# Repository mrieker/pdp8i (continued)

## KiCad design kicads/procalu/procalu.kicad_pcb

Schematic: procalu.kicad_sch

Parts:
C1, C2, C3, C4, C5, C6, C7, C8, C9, C10, C11, C12, C13, C14, C15, C16, C17, C18, C19, C20, C21, C22, C23, C24, C25, C26, C27, C28, C29, C30, C31, C32, C33, C34, C35, C36, C37, C38, C39, C40, C41, C42, C43, C44, C45, C46, C47, C48, C49, C50, C51, C52, C53, C54, C55, C56, C57, C58, C59, C60, C61, C62, C63, C64, C65, C66, C67, C68, C69, C70, C71, C72, C73, C74, C75, C76: C; R_Axial_DIN0207_L6.3mm_D2.5mm_P7.62mm_Horizontal
E11, E21, E31, E41, E51, E61, E71, E81, E91, E101, E111: 74AHC540; DIP-20_W7.62mm
E12, E42, E72: 74AHC86; DIP-14_W7.62mm
E13, E85: 74AHC138; DIP-16_W7.62mm
E14: 74AHC02
E15, E74, E87, E94, E103, E104: 74AHC04; DIP-14_W7.62mm
E16, E17, E18, E27, E68, E75, E95: 74AC10; DIP-14_W7.62mm
E22, E52, E73: 74AHC157; DIP-16_W7.62mm
E23, E24, E32, E36, E43, E44, E45, E56, E62, E63, E64, E82: 74AC153; DIP-16_W7.62mm
E25, E33, E46, E55, E66: 74AHC08; DIP-14_W7.62mm
E26: 74AC11; DIP-14_W7.62mm
E28, E78: 74AC20; DIP-14_W7.62mm
E34, E54, E65: 74AC283; DIP-16_W7.62mm
E35, E53, E67, E83: 74AHC32; DIP-14_W7.62mm
E37, E77: 74HC27; DIP-14_W7.62mm
E38, E57, E86, E88, E92, E96: 74AHC00; DIP-14_W7.62mm
E47: 74HC21; DIP-14_W7.62mm
E48, E84: 74AHC02; DIP-14_W7.62mm
E58, E76, E105: 74HC30; DIP-14_W7.62mm
E93: 74HC4075; DIP-14_W7.62mm
E102: 74HC42; DIP-16_W7.62mm
J1, J2, J3, J4: Conn_01x36; PinHeader_1x36_P2.54mm_Vertical

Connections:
/AA: E37.9, E38.6, E84.12
/BB: E74.9, E84.9, E105.8
/CC: E84.8, E95.8
/CC3: E92.12, E93.4, E94.10
/CONSCK: J4.35
/CONSDA: J4.34
/EE: E48.8, E68.8
/FF: E28.6, E48.2, E48.5, E48.9
/HH: E77.2, E77.10, E83.11
/JJ: E48.3, E48.6, E58.8, E77.11, E77.13
/KK: E26.8, E37.11
/LL: E77.9, E78.8
/MM: E18.8, E77.1
/NN: E15.8, E37.10, E57.1
/_AA1: E17.8, E38.4
/_AA2: E38.5, E88.6
/_ACCLEAR: E91.2 (A0), J3.28
/_ACUM_0: E81.4 (A2), J3.7
/_ACUM_1: E71.7 (A5), J2.34
/_ACUM_2: E71.2 (A0), J2.27
/_ACUM_3: E61.5 (A3), J2.20
/_ACUM_4: E51.8 (A6), J2.13
/_ACUM_5: E51.3 (A1), J2.7
/_ACUM_6: E41.6 (A4), J1.35
/_ACUM_7: E31.9 (A7), J1.29
/_ACUM_8: E31.4 (A2), J1.23
/_ACUM_9: E21.6 (A4), J1.16
/_ACUM_10: E11.8 (A6), J1.9
/_ACUM_11: E11.2 (A0), J1.2
/_BB1: E94.8, E105.2
/_BB2: E104.8, E105.6
/_BB3: E95.6, E105.12
/_BB4: E96.3, E105.11
/_BB5: E83.8, E105.1
/_BB6: E93.10, E105.3
/_BRKCYC: J4.33
/_BRKRQST: J3.29
/_BRKWRM: E101.2 (A0), J4.11
/_BUSINI: J3.31
/_BWCOV: J3.32
/_CAINC: E101.3 (A1), J4.12
/_CC1: E95.9, E96.6, E96.9
/_CC2: E95.10, E96.10, E96.11
/_CC3: E67.9, E75.8, E94.11, E95.11
/_CLOCK: J4.6
/_CYCLE3: E101.4 (A2), J4.13
/_DFLD_0: J3.22
/_DFLD_1: J3.18
/_DFLD_2: J3.14
/_DMAFLD_0: J3.23
/_EE1: E27.12, E68.10
/_EE2: E68.11, E68.12
/_EE3: E68.9, E88.8
/_FF1: E27.8, E28.2
/_FF2: E16.8, E28.1
/_FF3: E28.4, E38.3
/_FF4: E28.5, E95.12
/_IFLD_0: J3.24
/_IFLD_1: J3.20
/_IFLD_2: J3.16
/_INBUS_0: E81.7 (A5), J3.10
/_INBUS_1: E81.2 (A0), J3.3
/_INBUS_2: E71.5 (A3), J2.30
/_INBUS_3: E61.8 (A6), J2.23
/_INBUS_4: E61.3 (A1), J2.16
/_INBUS_5: E51.6 (A4), J2.10
/_INBUS_6: E41.9 (A7), J2.4
/_INBUS_7: E41.4 (A2), J1.32
/_INBUS_8: E31.7 (A5), J1.26
/_INBUS_9: E21.9 (A7), J1.19
/_INBUS_10: E21.3 (A1), J1.12
/_INBUS_11: E11.5 (A3), J1.5
/_INTINH: J4.15
/_INTRQST: J4.16
/_ION: J3.30
/_IOP: E91.8 (A6), J4.8
/_IOSKIP: J4.17
/_IREG_9: E31.3 (A1), J1.22
/_IREG_10: E21.5 (A3), J1.15
/_IREG_11: E11.7 (A5), J1.8
/_JJ1: E58.5, E92.3
/_JJ2: E57.8, E58.4
/_JJ3: E17.12, E58.1
/_JJ4: E58.6, E86.6
/_JJ5: E57.11, E58.3
/_JJ6: E38.8, E58.2
/_LINK: E91.9 (A7), J4.9
/_LL1: E17.6, E78.13
/_LL2: E78.10, E86.8
/_LL3: E78.9, E88.11
/_LL4: E68.6, E78.12
/_LNKTOG: J4.18
/_MADR_0: E81.5 (A3), J3.8
/_MADR_1: E71.8 (A6), J2.35
/_MADR_2: E71.3 (A1), J2.28
/_MADR_3: E61.6 (A4), J2.21
/_MADR_4: E51.9 (A7), J2.14
/_MADR_5: E51.4 (A2), J2.8
/_MADR_6: E41.7 (A5), J2.2
/_MADR_7: E41.2 (A0), J1.30
/_MADR_8: E31.5 (A3), J1.24
/_MADR_9: E21.7 (A5), J1.17
/_MADR_10: E11.9 (A7), J1.10
/_MADR_11: E11.3 (A1), J1.3
/_MAJST_0: E101.8 (A6), J4.22
/_MAJST_1: E101.7 (A5), J4.21
/_MAJST_2: E101.6 (A4), J4.20
/_MAJST_3: E101.5 (A3), J4.19
/_MBUF_0: E81.6 (A4), J3.9
/_MBUF_1: E71.9 (A7), J3.2
/_MBUF_2: E71.4 (A2), J2.29
/_MBUF_3: E61.7 (A5), J2.22
/_MBUF_4: E61.2 (A0), J2.15
/_MBUF_5: E51.5 (A3), J2.9
/_MBUF_6: E41.8 (A6), J2.3
/_MBUF_7: E41.3 (A1), J1.31
/_MBUF_8: E31.6 (A4), J1.25
/_MBUF_9: E21.8 (A6), J1.18
/_MBUF_10: E21.2 (A0), J1.11
/_MBUF_11: E11.4 (A2), J1.4
/_MEAD_0: J3.25
/_MEAD_1: J3.21
/_MEAD_2: J3.17
/_MEMDIS: J3.26
/_MM1: E18.6, E18.11
/_MM2: E18.9, E88.3
/_MM3: E18.10, E28.8
/_NN1: E15.9, E16.6, E27.3
/_PAUSE: J4.14
/_PCTR_0: E81.8 (A6), J3.12
/_PCTR_1: E81.3 (A1), J3.5
/_PCTR_2: E71.6 (A4), J2.32
/_PCTR_3: E61.9 (A7), J2.25
/_PCTR_4: E61.4 (A2), J2.18
/_PCTR_5: E51.7 (A5), J2.12
/_PCTR_6: E51.2 (A0), J2.6
/_PCTR_7: E41.5 (A3), J1.34
/_PCTR_8: E31.8 (A6), J1.28
/_PCTR_9: E31.2 (A0), J1.21
/_PCTR_10: E21.4 (A2), J1.14
/_PCTR_11: E11.6 (A4), J1.7
/_PP1: E74.13, E75.6
/_PP2: E16.12, E27.4
/_READSR: E81.11 (Y7), J3.27
/_RESET: J4.7
/_RUN: J4.10
/_SWCONT: E91.6 (A4), J4.2
/_SWDEPOS: E91.5 (A3), J3.35
/_SWEXAM: E91.4 (A2), J3.34
/_SWLDAD: E91.3 (A1), J3.33
/_SWSINST: J4.5
/_SWSSTEP: J4.4
/_SWSTART: E91.7 (A5), J4.3
/_TP1: J4.27
/_TP2: J4.28
/_TP3: J4.29
/_TP4: J4.30
/_TS1: E111.2 (A0), J4.23
/_TS2: E111.3 (A1), J4.24
/_TS3: E111.4 (A2), J4.25
/_TS4: E111.5 (A3), J4.26
/_asel_0: E23.14 (S0), E24.14 (S0), E32.14 (S0), E62.14 (S0), E63.14 (S0), E77.8, E78.5, E82.14 (S0)
/_asel_1: E23.2 (S1), E24.2 (S1), E32.2 (S1), E62.2 (S1), E63.2 (S1), E77.12, E78.4, E82.2 (S1)
/_bsel_0: E22.1 (S), E52.1 (S), E73.1 (S), E84.10
/_irand: E13.15 (~Y0), E74.1
/_irdca: E13.12 (~Y3), E15.5
/_iriot: E13.9 (~Y6)
/_irisz: E13.13 (~Y2), E15.13
/_irjmp: E13.10 (~Y5), E14.11, E15.11
/_irjms: E13.11 (~Y4), E15.3
/_iropr: E13.7 (~Y7), E14.8, E28.12, E77.4, E87.3
/_irtad: E13.14 (~Y1), E15.1
/_msdefer: E94.3, E102.3 (2)
/_msdepos: E102.10 (8), E103.9
/_msexec: E94.13, E102.4 (3)
/_msintak: E102.9 (7), E103.5
/_mswrdct: E74.11, E102.5 (4)
/_nxtmsbreak: E85.9 (~Y6), E93.12
/_nxtmswrdct: E83.10, E85.11 (~Y4)
/_ts4: E83.9, E93.13, E94.6
/acclear: E91.18 (Y0), E92.4
/acum_0: E72.9, E81.16 (Y2)
/acum_1: E71.13 (Y5), E72.5
/acum_2: E71.18 (Y0), E72.12
/acum_3: E61.15 (Y3), E72.1
/acum_4: E42.9, E51.12 (Y6)
/acum_5: E42.5, E51.17 (Y1)
/acum_6: E41.14 (Y4), E42.12
/acum_7: E31.11 (Y7), E42.1
/acum_8: E12.9, E31.16 (Y2)
/acum_9: E12.5, E21.14 (Y4)
/acum_10: E11.12 (Y6), E12.13
/acum_11: E11.18 (Y0), E12.1
/acxx_0: E72.8, E82.3 (I3a)
/acxx_1: E72.6, E82.13 (I3b)
/acxx_2: E63.3 (I3a), E72.11
/acxx_3: E63.13 (I3b), E72.3
/acxx_4: E42.8, E62.3 (I3a)
/acxx_5: E42.6, E62.13 (I3b)
/acxx_6: E32.3 (I3a), E42.11
/acxx_7: E32.13 (I3b), E42.3
/acxx_8: E12.8, E23.3 (I3a)
/acxx_9: E12.6, E23.13 (I3b)
/acxx_10: E12.11, E24.3 (I3a)
/acxx_11: E12.3, E24.13 (I3b)
/alua_0: E65.5 (A1), E66.4, E82.7 (Za), E83.2
/alua_1: E55.9, E65.3 (A2), E82.9 (Zb), E83.5
/alua_2: E63.7 (Za), E65.14 (A3), E66.2, E67.2
/alua_3: E63.9 (Zb), E65.12 (A4), E66.13, E67.4
/alua_4: E53.4, E54.5 (A1), E55.4, E62.7 (Za)
/alua_5: E53.9, E54.3 (A2), E55.2, E62.9 (Zb)
/alua_6: E32.7 (Za), E33.9, E53.12, E54.14 (A3)
/alua_7: E32.9 (Zb), E53.1, E54.12 (A4), E55.13
/alua_8: E23.7 (Za), E25.10, E34.5 (A1), E35.12
/alua_9: E23.9 (Zb), E25.13, E34.3 (A2), E35.1
/alua_10: E24.7 (Za), E34.14 (A3), E35.5, E46.5
/alua_11: E24.9 (Zb), E34.12 (A4), E35.10, E46.1
/alub_0: E65.6 (B1), E66.5, E73.4 (Za), E83.1
/alub_1: E55.10, E65.2 (B2), E73.7 (Zb), E83.4
/alub_2: E65.15 (B3), E66.1, E67.1, E73.9 (Zc)
/alub_3: E65.11 (B4), E66.12, E67.5, E73.12 (Zd)
/alub_4: E52.4 (Za), E53.5, E54.6 (B1), E55.5
/alub_5: E52.7 (Zb), E53.10, E54.2 (B2), E55.1
/alub_6: E33.10, E52.9 (Zc), E53.13, E54.15 (B3)
/alub_7: E52.12 (Zd), E53.2, E54.11 (B4), E55.12
/alub_8: E22.4 (Za), E25.9, E34.6 (B1), E35.13
/alub_9: E22.7 (Zb), E25.12, E34.2 (B2), E35.2
/alub_10: E22.9 (Zc), E34.15 (B3), E35.4, E46.4
/alub_11: E22.12 (Zd), E34.11 (B4), E35.9, E46.2
/aluq_0: E64.7 (Za), J3.11
/aluq_1: E64.9 (Zb), J3.4
/aluq_2: E56.7 (Za), J2.31
/aluq_3: E56.9 (Zb), J2.24
/aluq_4: E43.7 (Za), J2.17
/aluq_5: E43.9 (Zb), J2.11
/aluq_6: E44.7 (Za), J2.5
/aluq_7: E44.9 (Zb), J1.33
/aluq_8: E36.7 (Za), J1.27
/aluq_9: E36.9 (Zb), J1.20
/aluq_10: E45.7 (Za), J1.13
/aluq_11: E45.9 (Zb), J1.6
/aluq_12: J3.15
/autoinc: E27.10, E47.6
/azero: E23.1 (Ea), E23.15 (Eb), E24.1 (Ea), E24.15 (Eb), E32.1 (Ea), E32.15 (Eb), E62.1 (Ea), E62.15 (Eb), E63.1 (Ea), E63.15 (Eb), E75.12, E82.1 (Ea), E82.15 (Eb)
/brkwrm: E95.4, E101.18 (Y0)
/bzero: E22.15 (E), E52.15 (E), E73.15 (E), E78.6
/cainc: E95.1, E101.17 (Y1)
/cclears: E84.11, E92.8
/cin: E57.6, E65.7 (C0)
/comac: E12.2, E12.4, E12.10, E12.12, E26.12, E42.2, E42.4, E42.10, E42.13, E72.2, E72.4, E72.10, E72.13
/cout: E34.9 (C4), J3.19
/cycle3: E93.11, E101.16 (Y2)
/dirjmp: E14.13, E18.3
/efaddr_7: E32.11 (I1b), E33.6
/efaddr_8: E23.5 (I1a), E33.3
/efaddr_9: E23.11 (I1b), E33.11
/efaddr_10: E24.5 (I1a), E25.3
/efaddr_11: E24.11 (I1b), E25.6
/extarex: E86.11, E96.13
/group1: E14.10, E16.5, E26.2
/group2: E75.10, E77.6
/inbus_0: E73.2 (I0a), E81.13 (Y5)
/inbus_1: E73.5 (I0b), E81.18 (Y0)
/inbus_2: E71.15 (Y3), E73.11 (I0c)
/inbus_3: E61.12 (Y6), E73.14 (I0d)
/inbus_4: E52.2 (I0a), E61.17 (Y1)
/inbus_5: E51.14 (Y4), E52.5 (I0b)
/inbus_6: E41.11 (Y7), E52.11 (I0c)
/inbus_7: E41.16 (Y2), E52.14 (I0d)
/inbus_8: E22.2 (I0a), E31.13 (Y5)
/inbus_9: E21.11 (Y7), E22.5 (I0b)
/inbus_10: E21.17 (Y1), E22.11 (I0c)
/inbus_11: E11.15 (Y3), E22.14 (I0d)
/iop: E91.12 (Y6), E96.5
/irand: E74.2, E75.3
/irdca: E15.6, E17.11, E26.11
/ireg_9: E13.1 (A0), E31.17 (Y1)
/ireg_10: E13.2 (A1), E21.15 (Y3)
/ireg_11: E11.13 (Y5), E13.3 (A2)
/irisz: E15.12, E16.11
/irjmp: E15.10, E27.1
/irjms: E15.4, E17.2, E17.3
/iropr: E68.4, E76.11, E86.2, E87.4
/irtad: E15.2, E16.13
/link: E91.11 (Y7)
/madr_0: E81.15 (Y3), E82.6 (I0a)
/madr_1: E71.12 (Y6), E82.10 (I0b)
/madr_2: E63.6 (I0a), E71.17 (Y1)
/madr_3: E47.4, E61.14 (Y4), E63.10 (I0b)
/madr_4: E51.11 (Y7), E62.6 (I0a), E84.3
/madr_5: E51.16 (Y2), E62.10 (I0b), E84.2
/madr_6: E32.6 (I0a), E37.4, E41.13 (Y5)
/madr_7: E32.10 (I0b), E33.5, E37.5, E41.18 (Y0)
/madr_8: E23.6 (I0a), E31.15 (Y3), E33.1, E37.3
/madr_9: E21.13 (Y5), E23.10 (I0b), E33.12, E37.2
/madr_10: E11.11 (Y7), E24.6 (I0a), E25.1, E37.1
/madr_11: E11.17 (Y1), E24.10 (I0b), E25.5, E37.13
/majst_0: E101.12 (Y6), E102.15 (A0)
/majst_1: E101.13 (Y5), E102.14 (A1)
/majst_2: E101.14 (Y4), E102.13 (A2)
/majst_3: E84.5, E101.15 (Y3), E102.12 (A3)
/mbuf_0: E57.2, E73.3 (I1a), E76.3, E77.3, E81.14 (Y4), E82.5 (I1a)
/mbuf_1: E71.11 (Y7), E73.6 (I1b), E74.3, E82.11 (I1b)
/mbuf_2: E63.5 (I1a), E67.10, E71.16 (Y2), E73.10 (I1c), E74.5
/mbuf_3: E61.13 (Y5), E63.11 (I1b), E73.13 (I1d)
/mbuf_4: E52.3 (I1a), E61.18 (Y0), E62.5 (I1a)
/mbuf_5: E26.1, E51.15 (Y3), E52.6 (I1b), E62.11 (I1b)
/mbuf_6: E32.5 (I1a), E41.12 (Y6), E52.10 (I1c)
/mbuf_7: E25.2, E25.4, E33.2, E33.4, E33.13, E41.17 (Y1), E52.13 (I1d), E92.13
/mbuf_8: E14.9, E14.12, E22.3 (I1a), E31.14 (Y4), E76.12, E87.1
/mbuf_9: E21.12 (Y6), E22.6 (I1b)
/mbuf_10: E21.18 (Y0), E22.10 (I1c)
/mbuf_11: E11.16 (Y2), E22.13 (I1d)
/memacsw: J2.19
/msbreak: E95.5, E103.10
/mscurad: E88.9, E95.13, E103.12
/msdefer: E27.9, E27.13, E68.1, E94.4
/msdepos: E57.9, E66.9, E96.2, E103.8
/msexam: E92.2, E103.4
/msexec: E16.2, E16.10, E17.4, E17.10, E17.13, E26.9, E75.5, E86.1, E94.12
/msfetch: E16.3, E18.5, E26.13, E28.13, E75.9, E76.1, E103.2
/msintak: E86.4, E86.9, E103.6
/mswrdct: E38.1, E38.10, E57.13, E74.10
/nxtms_0: E85.1 (A0), J3.13
/nxtms_1: E85.2 (A1), J3.6
/nxtms_2: E85.3 (A2), J2.33
/nxtms_3: E85.4 (~E0), J2.26
/nxtmsdefer: E87.6, E88.2
/nxtmsexec: E28.9, E68.5, E68.13, E87.12
/nxtmsfetch: E87.10, E88.13
/nxtmsintak: E87.8, E88.5
/pctr_0: E81.12 (Y6), E82.4 (I2a)
/pctr_1: E81.17 (Y1), E82.12 (I2b)
/pctr_2: E63.4 (I2a), E71.14 (Y4)
/pctr_3: E61.11 (Y7), E63.12 (I2b)
/pctr_4: E61.16 (Y2), E62.4 (I2a)
/pctr_5: E51.13 (Y5), E62.12 (I2b)
/pctr_6: E32.4 (I2a), E51.18 (Y0)
/pctr_7: E32.12 (I2b), E41.15 (Y3)
/pctr_8: E23.4 (I2a), E31.12 (Y6)
/pctr_9: E23.12 (I2b), E31.18 (Y0)
/pctr_10: E21.16 (Y2), E24.4 (I2a)
/pctr_11: E11.14 (Y4), E24.12 (I2b)
/qsel_0: E36.14 (S0), E43.14 (S0), E44.14 (S0), E45.14 (S0), E56.14 (S0), E64.14 (S0), E74.12
/qsel_1: E27.6, E36.2 (S1), E43.2 (S1), E44.2 (S1), E45.2 (S1), E56.2 (S1), E64.2 (S1)
/qsum_0: E64.4 (I2a), E65.4 (S1)
/qsum_1: E64.12 (I2b), E65.1 (S2)
/qsum_2: E56.4 (I2a), E65.13 (S3)
/qsum_3: E56.12 (I2b), E65.10 (S4)
/readsr: E81.9 (A7), E93.6
/swcont: E91.14 (Y4), E94.1
/swcontx: E83.13, E84.4
/swdepos: E57.10, E91.15 (Y3)
/swexam: E91.16 (Y2), E92.1
/swldad: E91.17 (Y1), E93.5, E94.9
/swstart: E83.12, E91.13 (Y5)
/ts1: E104.9, E111.18 (Y0)
/ts2: E16.9, E17.5, E26.10, E27.11, E38.2, E66.10, E86.10, E95.2, E95.3, E96.1, E111.17 (Y1)
/ts3: E16.1, E16.4, E17.1, E17.9, E18.4, E27.2, E57.12, E75.4, E75.11, E86.5, E96.4, E96.12, E111.16 (Y2)
/ts4: E28.10, E38.9, E68.2, E68.3, E88.1, E88.4, E88.10, E88.12, E94.5, E111.15 (Y3)
GND: C1.2, C2.2, C3.2, C4.2, C5.2, C6.2, C7.2, C8.2, C9.2, C10.2, C11.2, C12.2, C13.2, C14.2, C15.2, C16.2, C17.2, C18.2, C19.2, C20.2, C21.2, C22.2, C23.2, C24.2, C25.2, C26.2, C27.2, C28.2, C29.2, C30.2, C31.2, C32.2, C33.2, C34.2, C35.2, C36.2, C37.2, C38.2, C39.2, C40.2, C41.2, C42.2, C43.2, C44.2, C45.2, C46.2, C47.2, C48.2, C49.2, C50.2, C51.2, C52.2, C53.2, C54.2, C55.2, C56.2, C57.2, C58.2, C59.2, C60.2, C61.2, C62.2, C63.2, C64.2, C65.2, C66.2, C67.2, C68.2, C69.2, C70.2, C71.2, C72.2, C73.2, C74.2, C75.2, C76.2, E11.1 (G1), E11.10 (GND), E11.19 (G2), E12.7 (GND), E13.4 (~E0), E13.5 (~E1), E13.8 (GND), E14.2, E14.3, E14.5, E14.6, E14.7 (GND), E15.7 (GND), E16.7 (GND), E17.7 (GND), E18.1, E18.2, E18.7 (GND), E18.13, E21.1 (G1), E21.10 (GND), E21.19 (G2), E22.8 (GND), E23.8 (GND), E24.8 (GND), E25.7 (GND), E26.3, E26.4, E26.5, E26.7 (GND), E27.7 (GND), E28.7 (GND), E31.1 (G1), E31.10 (GND), E31.19 (G2), E32.8 (GND), E33.7 (GND), E34.8 (GND), E35.7 (GND), E36.1 (Ea), E36.3 (I3a), E36.8 (GND), E36.13 (I3b), E36.15 (Eb), E37.7 (GND), E38.7 (GND), E38.12, E38.13, E41.1 (G1), E41.10 (GND), E41.19 (G2), E42.7 (GND), E43.1 (Ea), E43.3 (I3a), E43.8 (GND), E43.13 (I3b), E43.15 (Eb), E44.1 (Ea), E44.3 (I3a), E44.8 (GND), E44.13 (I3b), E44.15 (Eb), E45.1 (Ea), E45.3 (I3a), E45.8 (GND), E45.13 (I3b), E45.15 (Eb), E46.7 (GND), E46.9, E46.10, E46.12, E46.13, E47.7 (GND), E47.9, E47.10, E47.12, E47.13, E48.7 (GND), E48.11, E48.12, E51.1 (G1), E51.10 (GND), E51.19 (G2), E52.8 (GND), E53.7 (GND), E54.8 (GND), E55.7 (GND), E56.1 (Ea), E56.3 (I3a), E56.8 (GND), E56.13 (I3b), E56.15 (Eb), E57.7 (GND), E58.7 (GND), E61.1 (G1), E61.10 (GND), E61.19 (G2), E62.8 (GND), E63.8 (GND), E64.1 (Ea), E64.3 (I3a), E64.8 (GND), E64.13 (I3b), E64.15 (Eb), E65.8 (GND), E66.7 (GND), E67.7 (GND), E67.12, E67.13, E68.7 (GND), E71.1 (G1), E71.10 (GND), E71.19 (G2), E72.7 (GND), E73.8 (GND), E74.7 (GND), E75.7 (GND), E76.7 (GND), E77.7 (GND), E78.7 (GND), E81.1 (G1), E81.10 (GND), E81.19 (G2), E82.8 (GND), E83.7 (GND), E84.7 (GND), E85.5 (~E1), E85.8 (GND), E86.7 (GND), E87.7 (GND), E88.7 (GND), E91.1 (G1), E91.10 (GND), E91.19 (G2)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
unnamed: E27.5, E48.1
unnamed: E34.7 (C0), E54.9 (C4)
unnamed: E34.4 (S1), E36.4 (I2a)
unnamed: E34.1 (S2), E36.12 (I2b)
unnamed: E34.13 (S3), E45.4 (I2a)
unnamed: E34.10 (S4), E45.12 (I2b)
unnamed: E35.11, E36.6 (I0a)
unnamed: E35.3, E36.10 (I0b)
unnamed: E25.8, E36.5 (I1a)
unnamed: E25.11, E36.11 (I1b)
unnamed: E37.6, E47.2
unnamed: E37.8, E78.1
unnamed: E37.12, E47.1
unnamed: E43.6 (I0a), E53.6
unnamed: E43.10 (I0b), E53.8
unnamed: E43.5 (I1a), E55.6
unnamed: E43.11 (I1b), E55.3
unnamed: E43.4 (I2a), E54.4 (S1)
unnamed: E43.12 (I2b), E54.1 (S2)
unnamed: E44.6 (I0a), E53.11
unnamed: E44.10 (I0b), E53.3
unnamed: E33.8, E44.5 (I1a)
unnamed: E44.11 (I1b), E55.11
unnamed: E44.4 (I2a), E54.13 (S3)
unnamed: E44.12 (I2b), E54.10 (S4)
unnamed: E35.6, E45.6 (I0a)
unnamed: E35.8, E45.10 (I0b)
unnamed: E45.5 (I1a), E46.6
unnamed: E45.11 (I1b), E46.3
unnamed: E47.5, E84.1
unnamed: E48.4, E57.5
unnamed: E48.10, E75.13
unnamed: E54.7 (C0), E65.9 (C4)
unnamed: E56.6 (I0a), E67.3
unnamed: E56.10 (I0b), E67.6
unnamed: E56.5 (I1a), E66.3
unnamed: E56.11 (I1b), E66.11
unnamed: E57.3, E57.4
unnamed: E64.6 (I0a), E83.3
unnamed: E64.10 (I0b), E83.6
unnamed: E64.5 (I1a), E66.6
unnamed: E55.8, E64.11 (I1b)
unnamed: E66.8, E93.3
unnamed: E67.8, E78.2
unnamed: E74.4, E76.4
unnamed: E74.6, E76.6
unnamed: E74.8, E75.1
unnamed: E75.2, E84.13
unnamed: E76.8, E86.12
unnamed: E77.5, E87.2
unnamed: E84.6, E94.2
unnamed: E85.14 (~Y1), E87.11
unnamed: E85.13 (~Y2), E87.5
unnamed: E85.12 (~Y3), E87.13
unnamed: E85.7 (~Y7), E87.9
unnamed: E86.3, E86.13
unnamed: E92.5, E96.8
unnamed: E92.6, E92.9
unnamed: E92.10, E92.11
unnamed: E102.2 (1), E103.1
unnamed: E102.6 (5), E103.13
unnamed: E102.7 (6), E103.11
unnamed: E102.11 (9), E103.3
VCC: C1.1, C2.1, C3.1, C4.1, C5.1, C6.1, C7.1, C8.1, C9.1, C10.1, C11.1, C12.1, C13.1, C14.1, C15.1, C16.1, C17.1, C18.1, C19.1, C20.1, C21.1, C22.1, C23.1, C24.1, C25.1, C26.1, C27.1, C28.1, C29.1, C30.1, C31.1, C32.1, C33.1, C34.1, C35.1, C36.1, C37.1, C38.1, C39.1, C40.1, C41.1, C42.1, C43.1, C44.1, C45.1, C46.1, C47.1, C48.1, C49.1, C50.1, C51.1, C52.1, C53.1, C54.1, C55.1, C56.1, C57.1, C58.1, C59.1, C60.1, C61.1, C62.1, C63.1, C64.1, C65.1, C66.1, C67.1, C68.1, C69.1, C70.1, C71.1, C72.1, C73.1, C74.1, C75.1, C76.1, E11.20 (VCC), E12.14 (VCC), E13.6 (E2), E13.16 (VCC), E14.14 (VCC), E15.14 (VCC), E16.14 (VCC), E17.14 (VCC), E18.14 (VCC), E21.20 (VCC), E22.16 (VCC), E23.16 (VCC), E24.16 (VCC), E25.14 (VCC), E26.14 (VCC), E27.14 (VCC), E28.14 (VCC), E31.20 (VCC), E32.16 (VCC), E33.14 (VCC), E34.16 (VCC), E35.14 (VCC), E36.16 (VCC), E37.14 (VCC), E38.14 (VCC), E41.20 (VCC), E42.14 (VCC), E43.16 (VCC), E44.16 (VCC), E45.16 (VCC), E46.14 (VCC), E47.14 (VCC), E48.14 (VCC), E51.20 (VCC), E52.16 (VCC), E53.14 (VCC), E54.16 (VCC), E55.14 (VCC), E56.16 (VCC), E57.14 (VCC), E58.11, E58.12, E58.14 (VCC), E61.20 (VCC), E62.16 (VCC), E63.16 (VCC), E64.16 (VCC), E65.16 (VCC), E66.14 (VCC), E67.14 (VCC), E68.14 (VCC), E71.20 (VCC), E72.14 (VCC), E73.16 (VCC), E74.14 (VCC), E75.14 (VCC), E76.2, E76.5, E76.14 (VCC), E77.14 (VCC), E78.14 (VCC), E81.20 (VCC), E82.16 (VCC), E83.14 (VCC), E84.14 (VCC), E85.6 (E2), E85.16 (VCC), E86.14 (VCC), E87.14 (VCC), E88.14 (VCC), E91.20 (VCC), E92.14 (VCC), E93.14 (VCC), E94.14 (VCC), E95.14 (VCC), E96.14 (VCC), E101.20 (VCC), E102.16 (VCC), E103.14 (VCC), E104.14 (VCC), E105.4, E105.5, E105.14 (VCC), E111.20 (VCC), J1.1, J2.1, J3.1, J4.1

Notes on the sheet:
TS3: ACUM <= ACUM + MBUF
TS4: MADR <= MBUF
TS3: PCTR <= MBUF
TS4: MADR <= INBUS (dma addr)
TS2: MBUF <= INBUS (dma data)
TS4: MADR <= 0
sets ALU to compute MADR + 1 _JJ5 sets up the add in TS3 but does not clock into MADR at TP3 _JJ6 continues the add in TS4 then gets clocked into MADR at TP4
(efaddr_2)
// _MQUO_0
TS3: ACUM <= ACUM | INBUS (io data)
gate SWREG onto INBUS * during TS3 of Group2 for OSR * while LDAD held down to load MADR * during TS2 while doing deposit
// _SCTR_1
// _SCTR_2
TS3: ACUM <= 0
// _MQUO_2
TS3: PCTR <= MADR + 1
LSB
(efaddr_0)
TS2: MBUF <= INBUS (swREG)
// _MQUO_5
// _SCTR_4
// _DMAFLD_2
// _DMAFLD_1
// _MQUO_8
asserted (low) when doing Group2 CLA
TS3 msfetch group1 IAC
// _MQUO_10
MSB
TS1: MBUF <= INBUS (mem data)
(efaddr_3)
// _MQUO_4
TS2: MBUF <= PCTR
// _MQUO_11
TS4: MADR <= efaddr
(efaddr_1)
TS4: MADR <= PCTR
low when doing Group2 with OSR bit low blocking SR coming in on INBUS
TS3: ACUM <= ACUM & MBUF
TS3: PCTR <= efaddr
// _MQUO_3

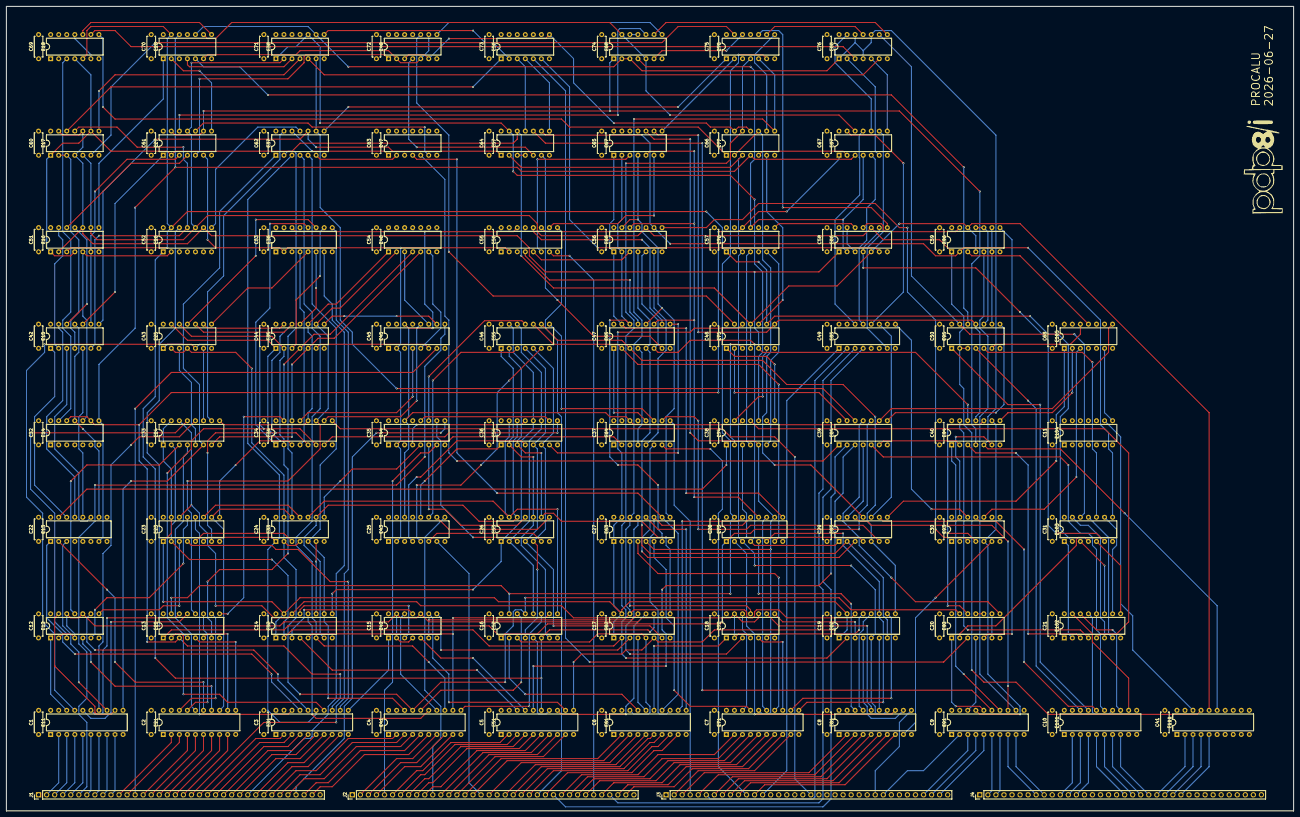
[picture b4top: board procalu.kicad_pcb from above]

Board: 4 copper layers, 406.4 x 254.0 mm, 156 parts (0 on the bottom side), 389 nets.

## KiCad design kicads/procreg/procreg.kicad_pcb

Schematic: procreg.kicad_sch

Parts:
C11, C12, C13, C14, C15, C16, C17, C18, C21, C22, C23, C24, C25, C26, C27, C28, C31, C32, C33, C34, C35, C36, C37, C38, C41, C42, C43, C44, C45, C46, C47, C48, C51, C52, C53, C54, C55, C56, C57, C58, C61, C62, C63, C64, C65, C66, C67, C68, C71, C72, C73, C74, C75, C76, C77, C78, C81, C82, C83, C84, C85, C86, C87, C88, C91, C92, C93, C94, C95, C96, C101: C; R_Axial_DIN0207_L6.3mm_D2.5mm_P7.62mm_Horizontal
E11, E21, E31, E41, E51, E61, E71, E81, E91, E101: 74AHC540; DIP-20_W7.62mm
E12, E13, E24, E34, E45, E52: 74AHC174; DIP-16_W7.62mm
E14, E15, E16, E17, E18, E25, E26, E27, E28, E35, E36, E37, E38: 74AC151; DIP-16_W7.62mm
E22, E42, E53: 74AC161; DIP-16_W7.62mm
E23, E33, E78: 74HC27; DIP-14_W7.62mm
E32: 74HC175; DIP-16_W7.62mm
E43, E67, E96: 74HC30; DIP-14_W7.62mm
E44: 74HC21; DIP-14_W7.62mm
E46: 74AHC138; DIP-16_W7.62mm
E47, E83, E87, E95: 74AHC04; DIP-14_W7.62mm
E48, E74, E76: 74AC10; DIP-14_W7.62mm
E54, E73: 74AHC08; DIP-14_W7.62mm
E55, E57, E58, E63, E75, E77, E84, E85, E92, E93: 74AHC00; DIP-14_W7.62mm
E56: 74AHC02; DIP-14_W7.62mm
E62, E66, E86: 74AC20; DIP-14_W7.62mm
E64: 74AHC86; DIP-14_W7.62mm
E65: 74AC11; DIP-14_W7.62mm
E68: 74AHC04
E72: 74AHC74
E82: 74AHC74; DIP-14_W7.62mm
E88: 74AHC32; DIP-14_W7.62mm
E94: 74HC42; DIP-16_W7.62mm
J1, J2, J3, J4: Conn_01x36; PinHeader_1x36_P2.54mm_Vertical

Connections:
/CONSCK: J4.35
/CONSDA: J4.34
/_ACCLEAR: J3.28
/_ACUM_0: E71.16 (Y2), J3.7
/_ACUM_1: E61.12 (Y6), J2.34
/_ACUM_2: E61.16 (Y2), J2.27
/_ACUM_3: E51.12 (Y6), J2.20
/_ACUM_4: E51.16 (Y2), J2.13
/_ACUM_5: E41.12 (Y6), J2.7
/_ACUM_6: E41.16 (Y2), J1.35
/_ACUM_7: E31.12 (Y6), J1.29
/_ACUM_8: E31.16 (Y2), J1.23
/_ACUM_9: E21.14 (Y4), J1.16
/_ACUM_10: E11.12 (Y6), J1.9
/_ACUM_11: E11.18 (Y0), J1.2
/_BRKCYC: E101.11 (Y7), J4.33
/_BRKRQST: J3.29
/_BRKWRM: E81.9 (A7), J4.11
/_BUSINI: E71.8 (A6), J3.31
/_BWCOV: E71.11 (Y7), J3.32
/_CAINC: E91.2 (A0), J4.12
/_CLOCK: J4.6
/_CYCLE3: J4.13
/_DFLD_0: J3.22
/_DFLD_1: J3.18
/_DFLD_2: J3.14
/_DMAFLD_0: J3.23
/_DMAFLD_2: J3.15
/_IFLD_0: J3.24
/_IFLD_1: J3.20
/_IFLD_2: J3.16
/_INBUS_0: J3.10
/_INBUS_1: J3.3
/_INBUS_2: J2.30
/_INBUS_3: J2.23
/_INBUS_4: J2.16
/_INBUS_5: J2.10
/_INBUS_6: J2.4
/_INBUS_7: J1.32
/_INBUS_8: J1.26
/_INBUS_9: E21.9 (A7), J1.19
/_INBUS_10: E21.3 (A1), J1.12
/_INBUS_11: E11.5 (A3), J1.5
/_INTINH: J4.15
/_INTRQST: J4.16
/_ION: J3.30
/_IOP: E81.6 (A4), J4.8
/_IOSKIP: E91.3 (A1), J4.17
/_IREG_9: E31.17 (Y1), J1.22
/_IREG_10: E21.15 (Y3), J1.15
/_IREG_11: E11.13 (Y5), J1.8
/_LINK: E81.13 (Y5), J4.9
/_LNKTOG: E91.4 (A2), J4.18
/_MADR_0: E71.15 (Y3), J3.8
/_MADR_1: E61.11 (Y7), J2.35
/_MADR_2: E61.15 (Y3), J2.28
/_MADR_3: E51.11 (Y7), J2.21
/_MADR_4: E51.15 (Y3), J2.14
/_MADR_5: E41.11 (Y7), J2.8
/_MADR_6: E41.15 (Y3), J2.2
/_MADR_7: E31.11 (Y7), J1.30
/_MADR_8: E31.15 (Y3), J1.24
/_MADR_9: E21.13 (Y5), J1.17
/_MADR_10: E11.11 (Y7), J1.10
/_MADR_11: E11.17 (Y1), J1.3
/_MAJST_0: E91.8 (A6), J4.22
/_MAJST_1: E91.7 (A5), J4.21
/_MAJST_2: E91.6 (A4), J4.20
/_MAJST_3: E91.5 (A3), J4.19
/_MBUF_0: E71.14 (Y4), J3.9
/_MBUF_1: E71.18 (Y0), J3.2
/_MBUF_2: E61.14 (Y4), J2.29
/_MBUF_3: E61.18 (Y0), J2.22
/_MBUF_4: E51.14 (Y4), J2.15
/_MBUF_5: E51.18 (Y0), J2.9
/_MBUF_6: E41.14 (Y4), J2.3
/_MBUF_7: E41.18 (Y0), J1.31
/_MBUF_8: E31.14 (Y4), J1.25
/_MBUF_9: E21.12 (Y6), J1.18
/_MBUF_10: E21.18 (Y0), J1.11
/_MBUF_11: E11.16 (Y2), J1.4
/_MEAD_0: J3.25
/_MEAD_1: J3.21
/_MEAD_2: J3.17
/_MEMDIS: J3.26
/_PAUSE: J4.14
/_PCTR_0: E71.13 (Y5), J3.12
/_PCTR_1: E71.17 (Y1), J3.5
/_PCTR_2: E61.13 (Y5), J2.32
/_PCTR_3: E61.17 (Y1), J2.25
/_PCTR_4: E51.13 (Y5), J2.18
/_PCTR_5: E51.17 (Y1), J2.12
/_PCTR_6: E41.13 (Y5), J2.6
/_PCTR_7: E41.17 (Y1), J1.34
/_PCTR_8: E31.13 (Y5), J1.28
/_PCTR_9: E31.18 (Y0), J1.21
/_PCTR_10: E21.16 (Y2), J1.14
/_PCTR_11: E11.14 (Y4), J1.7
/_READSR: J3.27
/_RESET: J4.7
/_RUN: E81.8 (A6), J4.10
/_SCTR_0: J3.13
/_SCTR_1: J3.6
/_SCTR_2: J2.33
/_SCTR_3: J2.26
/_SWCONT: E81.5 (A3), J4.2
/_SWDEPOS: E81.4 (A2), J3.35
/_SWEXAM: E81.3 (A1), J3.34
/_SWLDAD: E81.2 (A0), J3.33
/_SWSINST: J4.5
/_SWSSTEP: J4.4
/_SWSTART: J4.3
/_TP1: E101.5 (A3), J4.27
/_TP2: E101.6 (A4), J4.28
/_TP3: E101.7 (A5), J4.29
/_TP4: E101.8 (A6), J4.30
/_TS1: E91.9 (A7), J4.23
/_TS2: E101.2 (A0), J4.24
/_TS3: E101.3 (A1), J4.25
/_TS4: E101.4 (A2), J4.26
/_busini: E54.5, E73.2, E82.13 (~R), E83.4
/_extarex: E76.5, E85.9, E86.2, E95.12
/_irand: E46.15 (~Y0), E48.10
/_irdca: E46.12 (~Y3), E48.11, E48.13
/_iriot: E46.9 (~Y6)
/_irisz: E46.13 (~Y2), E47.13, E48.1
/_irjmp: E46.10 (~Y5), E56.12, E68.11
/_irjms: E46.11 (~Y4), E47.3, E48.2
/_iropr: E46.7 (~Y7), E56.8, E68.5, E78.1
/_irtad: E46.14 (~Y1), E47.11, E48.9
/_ldadclk: E63.3, E63.4, E74.3
/_msdefer: E87.3, E94.3 (2)
/_msdepos: E94.10 (8), E95.11, E96.4
/_msexec: E84.10, E87.1, E94.4 (3)
/_msintak: E47.9, E66.4, E94.9 (7), E96.2
/_mswrdct: E84.9, E94.5 (4), E96.3
/_pcld: E22.9 (~PE), E42.9 (~PE), E53.9 (~PE), E54.3
/_rsel_0: E14.11 (S0), E15.11 (S0), E16.11 (S0), E17.11 (S0), E18.11 (S0), E25.11 (S0), E26.11 (S0), E27.11 (S0), E28.11 (S0), E35.11 (S0), E36.11 (S0), E37.11 (S0), E38.11 (S0), E55.3
/_rsel_1: E14.10 (S1), E15.10 (S1), E16.10 (S1), E17.10 (S1), E18.10 (S1), E25.10 (S1), E26.10 (S1), E27.10 (S1), E28.10 (S1), E35.10 (S1), E36.10 (S1), E37.10 (S1), E38.10 (S1), E55.8
/_rsel_2: E14.9 (S2), E15.9 (S2), E16.9 (S2), E17.9 (S2), E18.9 (S2), E25.9 (S2), E26.9 (S2), E27.9 (S2), E28.9 (S2), E35.9 (S2), E36.9 (S2), E37.9 (S2), E38.9 (S2), E55.11
/_skiplnk: E63.8, E74.2
/_skipneg: E63.11, E74.1
/_skipzer: E43.8, E74.13
/acclk: E24.9 (Cp), E34.9 (Cp), E73.11
/acum_0: E33.11, E34.2 (Q0), E71.4 (A2)
/acum_1: E33.10, E34.5 (Q1), E61.8 (A6)
/acum_2: E33.9, E34.7 (Q2), E61.4 (A2)
/acum_3: E33.5, E34.10 (Q3), E51.8 (A6)
/acum_4: E33.4, E34.12 (Q4), E51.4 (A2)
/acum_5: E33.3, E34.15 (Q5), E41.8 (A6)
/acum_6: E24.2 (Q0), E33.13, E41.4 (A2)
/acum_7: E24.5 (Q1), E31.8 (A6), E33.2
/acum_8: E24.7 (Q2), E31.4 (A2), E33.1
/acum_9: E21.6 (A4), E23.9, E24.10 (Q3)
/acum_10: E11.8 (A6), E23.11, E24.12 (Q4)
/acum_11: E11.2 (A0), E23.10, E24.15 (Q5), E63.13
/aluq_0: E16.13 (I6), E18.15 (I4), E26.14 (I5), E27.2 (I2), E36.12 (I7), E37.1 (I3), E45.3 (D0), E52.3 (D0), E53.3 (D0), J3.11
/aluq_1: E15.13 (I6), E17.15 (I4), E18.14 (I5), E26.12 (I7), E36.1 (I3), E37.2 (I2), E45.4 (D1), E52.4 (D1), E53.4 (D1), J3.4
/aluq_2: E14.13 (I6), E17.14 (I5), E18.12 (I7), E26.1 (I3), E35.15 (I4), E36.2 (I2), E45.6 (D2), E52.6 (D2), E53.5 (D2), J2.31
/aluq_3: E17.12 (I7), E18.1 (I3), E25.15 (I4), E26.2 (I2), E35.14 (I5), E38.13 (I6), E45.11 (D3), E52.11 (D3), E53.6 (D3), J2.24
/aluq_4: E16.15 (I4), E17.1 (I3), E18.2 (I2), E25.14 (I5), E28.13 (I6), E35.12 (I7), E42.3 (D0), E45.13 (D4), E52.13 (D4), J2.17
/aluq_5: E15.15 (I4), E16.14 (I5), E17.2 (I2), E25.12 (I7), E27.13 (I6), E35.1 (I3), E42.4 (D1), E45.14 (D5), E52.14 (D5), J2.11
/aluq_6: E12.3 (D0), E13.3 (D0), E14.15 (I4), E15.14 (I5), E16.12 (I7), E25.1 (I3), E35.2 (I2), E36.13 (I6), E42.5 (D2), J2.5
/aluq_7: E12.4 (D1), E13.4 (D1), E14.14 (I5), E15.12 (I7), E16.1 (I3), E25.2 (I2), E26.13 (I6), E38.15 (I4), E42.6 (D3), J1.33
/aluq_8: E12.6 (D2), E13.6 (D2), E14.12 (I7), E15.1 (I3), E16.2 (I2), E18.13 (I6), E22.3 (D0), E28.15 (I4), E38.14 (I5), J1.27
/aluq_9: E12.11 (D3), E13.11 (D3), E14.1 (I3), E15.2 (I2), E17.13 (I6), E22.4 (D1), E27.15 (I4), E28.14 (I5), E38.12 (I7), J1.20
/aluq_10: E12.13 (D4), E13.13 (D4), E14.2 (I2), E22.5 (D2), E27.14 (I5), E28.12 (I7), E35.13 (I6), E37.15 (I4), E38.1 (I3), J1.13
/aluq_11: E12.14 (D5), E13.14 (D5), E22.6 (D3), E25.13 (I6), E27.12 (I7), E28.1 (I3), E36.15 (I4), E37.14 (I5), E38.2 (I2), J1.6
/aluq_12: E26.15 (I4), E27.1 (I3), E28.2 (I2), E36.14 (I5), E37.12 (I7), E37.13 (I6), E64.3
/autoinc: E44.6, E77.10
/brkcyc: E82.9 (Q), E101.9 (A7)
/brkwrm: E81.11 (Y7), E92.1
/busini: E71.12 (Y6), E83.3
/bwcov: E48.4, E71.9 (A7), E72.5 (Q)
/cainc: E91.18 (Y0), E93.9
/comln: E64.4, E65.6
/cout: E64.1, E72.2 (D), J3.19
/dirjmp: E56.13, E57.4
/extarex: E77.6, E93.13, E95.13
/g2skip: E64.8, E76.1
/group1: E56.10, E62.4, E62.10, E65.4, E65.13, E75.12, E88.2
/group2: E76.13, E78.12, E88.1
/inbus_9: E21.11 (Y7), E32.5 (D1)
/inbus_10: E21.17 (Y1), E32.12 (D2)
/inbus_11: E11.15 (Y3), E47.1
/iop: E75.9, E81.14 (Y4), E87.5
/ioskip: E75.10, E76.9, E91.17 (Y1)
/irandtaddca: E48.8, E58.13
/ireg_9: E31.3 (A1), E32.7 (Q1), E46.1 (A0)
/ireg_10: E21.5 (A3), E32.10 (Q2), E46.2 (A1)
/ireg_11: E11.7 (A5), E32.14 (~Q3), E46.3 (A2)
/irisz: E47.12, E48.3
/irjmp: E68.10, E77.13
/irjms: E47.4, E57.10
/iropr: E67.6, E68.6, E76.11, E77.1
/irtad: E47.10, E58.1
/link: E63.9, E64.5, E81.7 (A5), E82.5 (Q)
/lnclk: E73.8, E82.3 (C)
/lndat: E82.2 (D), E93.3
/lnktog: E91.16 (Y2), E93.12
/madr_0: E52.2 (Q0), E71.5 (A3)
/madr_1: E52.5 (Q1), E61.9 (A7)
/madr_2: E52.7 (Q2), E61.5 (A3)
/madr_3: E44.5, E51.9 (A7), E52.10 (Q3)
/madr_4: E51.5 (A3), E52.12 (Q4), E56.3
/madr_5: E41.9 (A7), E52.15 (Q5), E56.2
/madr_6: E13.2 (Q0), E23.5, E41.5 (A3)
/madr_7: E13.5 (Q1), E23.4, E31.9 (A7)
/madr_8: E13.7 (Q2), E23.3, E31.5 (A3)
/madr_9: E13.10 (Q3), E21.7 (A5), E23.2
/madr_10: E11.9 (A7), E13.12 (Q4), E23.1
/madr_11: E11.3 (A1), E13.15 (Q5), E23.13
/majst_0: E91.12 (Y6), E94.15 (A0)
/majst_1: E91.13 (Y5), E94.14 (A1)
/majst_2: E91.14 (Y4), E94.13 (A2)
/majst_3: E56.5, E83.9, E91.15 (Y3), E94.12 (A3)
/maload: E13.9 (Cp), E52.9 (Cp), E63.6
/mbload: E12.9 (Cp), E45.9 (Cp), E57.11
/mbuf_0: E45.2 (Q0), E67.5, E71.6 (A4), E78.2
/mbuf_1: E45.5 (Q1), E55.1, E68.1, E71.2 (A0)
/mbuf_2: E45.7 (Q2), E55.10, E61.6 (A4), E68.3
/mbuf_3: E45.10 (Q3), E55.13, E61.2 (A0), E64.10
/mbuf_4: E45.12 (Q4), E51.6 (A4), E63.10, E65.3
/mbuf_5: E43.6, E45.15 (Q5), E51.2 (A0)
/mbuf_6: E12.2 (Q0), E41.6 (A4), E62.13, E63.12
/mbuf_7: E12.5 (Q1), E41.2 (A0), E62.1
/mbuf_8: E12.7 (Q2), E31.6 (A4), E56.9, E56.11, E67.1, E68.9
/mbuf_9: E12.10 (Q3), E21.8 (A6)
/mbuf_10: E12.12 (Q4), E21.2 (A0)
/mbuf_11: E11.4 (A2), E12.15 (Q5)
/memacsw: E63.1, J2.19
/msbreak: E83.6, E92.2, E92.4
/mscurad: E93.10, E95.6
/msdefer: E77.9, E77.12, E87.4
/msdepos: E84.2, E95.10
/msexam: E84.5, E95.4
/msexec: E48.5, E57.9, E58.2, E58.5, E58.12, E76.10, E77.2, E87.2
/msfetch: E54.9, E57.5, E62.2, E62.12, E65.2, E67.2, E75.13, E76.2, E84.13, E85.1, E85.12, E95.2
/msintak: E47.8, E57.2
/pcclk: E22.2 (CP), E42.2 (CP), E53.2 (CP), E74.6
/pcinc: E22.7 (CEP), E42.7 (CEP), E53.7 (CEP), E53.10 (CET), E75.6
/pctr_0: E53.14 (Q0), E71.7 (A5)
/pctr_1: E53.13 (Q1), E71.3 (A1)
/pctr_2: E53.12 (Q2), E61.7 (A5)
/pctr_3: E53.11 (Q3), E61.3 (A1)
/pctr_4: E42.14 (Q0), E51.7 (A5)
/pctr_5: E42.13 (Q1), E51.3 (A1)
/pctr_6: E41.7 (A5), E42.12 (Q2)
/pctr_7: E41.3 (A1), E42.11 (Q3)
/pctr_8: E22.14 (Q0), E31.7 (A5)
/pctr_9: E22.13 (Q1), E31.2 (A0)
/pctr_10: E21.4 (A2), E22.12 (Q2)
/pctr_11: E11.6 (A4), E22.11 (Q3)
/rotq_0: E34.3 (D0), E36.5 (Z)
/rotq_1: E26.5 (Z), E34.4 (D1)
/rotq_2: E18.5 (Z), E34.6 (D2)
/rotq_3: E17.5 (Z), E34.11 (D3)
/rotq_4: E34.13 (D4), E35.5 (Z)
/rotq_5: E25.5 (Z), E34.14 (D5)
/rotq_6: E16.5 (Z), E24.3 (D0)
/rotq_7: E15.5 (Z), E24.4 (D1)
/rotq_8: E14.5 (Z), E24.6 (D2)
/rotq_9: E24.11 (D3), E38.5 (Z)
/rotq_10: E24.13 (D4), E28.5 (Z)
/rotq_11: E24.14 (D5), E27.5 (Z)
/rotq_12: E37.5 (Z), E85.10
/run: E54.2, E81.12 (Y6)
/swcont: E81.15 (Y3), E83.11
/swcontx: E56.4
/swdepos: E81.16 (Y2), E84.1
/swexam: E81.17 (Y1), E84.4
/swldad: E81.18 (Y0), E83.1
/tp1: E47.5, E54.10, E57.1, E101.15 (Y3)
/tp2: E62.5, E62.9, E73.4, E84.12, E85.4, E101.14 (Y4)
/tp3: E73.9, E73.12, E83.13, E101.13 (Y5)
/tp4: E92.12, E101.12 (Y6)
/ts1: E91.11 (Y7), E92.5
/ts2: E85.2, E101.18 (Y0)
/ts3: E55.5, E65.1, E65.5, E75.2, E101.17 (Y1)
/ts4: E82.11 (C), E101.16 (Y2)
GND: C11.2, C12.2, C13.2, C14.2, C15.2, C16.2, C17.2, C18.2, C21.2, C22.2, C23.2, C24.2, C25.2, C26.2, C27.2, C28.2, C31.2, C32.2, C33.2, C34.2, C35.2, C36.2, C37.2, C38.2, C41.2, C42.2, C43.2, C44.2, C45.2, C46.2, C47.2, C48.2, C51.2, C52.2, C53.2, C54.2, C55.2, C56.2, C57.2, C58.2, C61.2, C62.2, C63.2, C64.2, C65.2, C66.2, C67.2, C68.2, C71.2, C72.2, C73.2, C74.2, C75.2, C76.2, C77.2, C78.2, C81.2, C82.2, C83.2, C84.2, C85.2, C86.2, C87.2, C88.2, C91.2, C92.2, C93.2, C94.2, C95.2, C96.2, C101.2, E11.1 (G1), E11.10 (GND), E11.19 (G2), E12.8 (GND), E13.8 (GND), E14.3 (I1), E14.4 (I0), E14.7 (~E), E14.8 (GND), E15.3 (I1), E15.4 (I0), E15.7 (~E), E15.8 (GND), E16.3 (I1), E16.4 (I0), E16.7 (~E), E16.8 (GND), E17.3 (I1), E17.4 (I0), E17.7 (~E), E17.8 (GND), E18.3 (I1), E18.4 (I0), E18.7 (~E), E18.8 (GND), E21.1 (G1), E21.10 (GND), E21.19 (G2), E22.8 (GND), E23.7 (GND), E24.8 (GND), E25.3 (I1), E25.4 (I0), E25.7 (~E), E25.8 (GND), E26.3 (I1), E26.4 (I0), E26.7 (~E), E26.8 (GND), E27.3 (I1), E27.4 (I0), E27.7 (~E), E27.8 (GND), E28.3 (I1), E28.4 (I0), E28.7 (~E), E28.8 (GND), E31.1 (G1), E31.10 (GND), E31.19 (G2), E32.8 (GND), E33.7 (GND), E34.8 (GND), E35.3 (I1), E35.4 (I0), E35.7 (~E), E35.8 (GND), E36.3 (I1), E36.4 (I0), E36.7 (~E), E36.8 (GND), E37.3 (I1), E37.4 (I0), E37.7 (~E), E37.8 (GND), E38.3 (I1), E38.4 (I0), E38.7 (~E), E38.8 (GND), E41.1 (G1), E41.10 (GND), E41.19 (G2), E42.8 (GND), E43.7 (GND), E44.7 (GND), E44.9, E44.10, E44.12, E44.13, E45.8 (GND), E46.4 (~E0), E46.5 (~E1), E46.8 (GND), E47.7 (GND), E48.7 (GND), E51.1 (G1), E51.10 (GND), E51.19 (G2), E52.8 (GND), E53.8 (GND), E54.7 (GND), E54.12, E54.13, E55.7 (GND), E56.7 (GND), E57.7 (GND), E58.7 (GND), E58.9, E58.10, E61.1 (G1), E61.10 (GND), E61.19 (G2), E62.7 (GND), E63.7 (GND), E64.7 (GND), E64.12, E64.13, E65.7 (GND), E65.9, E65.10, E65.11, E66.7 (GND), E67.7 (GND), E68.7 (GND), E68.13, E71.1 (G1), E71.10 (GND), E71.19 (G2), E72.7 (GND), E72.10 (~S), E72.11 (C), E72.12 (D), E72.13 (~R), E73.7 (GND), E74.7 (GND), E75.7 (GND), E76.7 (GND), E77.7 (GND), E78.3, E78.4, E78.5, E78.7 (GND), E78.9, E78.10, E78.11, E81.1 (G1), E81.10 (GND), E81.19 (G2), E82.7 (GND)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
unnamed: E75.5, E85.3
unnamed: E57.12, E85.6
unnamed: E73.5, E84.8
unnamed: E75.3, E75.4
unnamed: E64.2, E64.6
unnamed: E72.3 (C), E73.6
unnamed: E48.6, E66.13
unnamed: E48.12, E58.4
unnamed: E47.6, E57.13
unnamed: E63.2, E74.8
unnamed: E63.5, E92.11
unnamed: E92.3, E96.5
unnamed: E83.8, E92.13
unnamed: E85.8, E93.1
unnamed: E93.8, E96.6
unnamed: E93.2, E93.11
unnamed: E85.13, E88.3
unnamed: E58.3, E76.3
unnamed: E75.11, E76.4
unnamed: E73.10, E76.6
unnamed: E66.9, E76.8
unnamed: E66.10, E76.12
unnamed: E74.4, E83.12
unnamed: E74.5, E84.11
unnamed: E74.9, E84.6
unnamed: E74.10, E84.3
unnamed: E74.11, E83.2
unnamed: E64.9, E74.12
unnamed: E58.6, E96.1
unnamed: E58.11, E86.1
unnamed: E94.2 (1), E95.1
unnamed: E94.6 (5), E95.5
unnamed: E83.5, E94.7 (6)
unnamed: E94.11 (9), E95.3
unnamed: E85.5, E96.8
unnamed: E77.8, E96.12
unnamed: E57.6, E66.1
unnamed: E57.8, E66.2
unnamed: E66.5, E77.11
unnamed: E55.4, E66.6
unnamed: E66.8, E75.1
unnamed: E66.12, E75.8
unnamed: E56.6, E83.10
unnamed: E54.1, E55.6
unnamed: E55.2, E55.9, E55.12, E65.12
unnamed: E85.11, E86.4
unnamed: E86.5, E87.6
unnamed: E73.13, E86.6
unnamed: E54.4, E62.6
unnamed: E62.8, E73.1
unnamed: E77.3, E77.4
unnamed: E67.8, E77.5
unnamed: E42.10 (CET), E53.15 (TC)
unnamed: E22.10 (CET), E42.15 (TC)
unnamed: E24.1 (~Mr), E34.1 (~Mr), E54.6
unnamed: E73.3, E82.1 (~R)
unnamed: E82.10 (~S), E92.6
unnamed: E32.9 (Cp), E54.8
unnamed: E32.13 (D3), E47.2
unnamed: E32.1 (~Mr), E57.3
unnamed: E67.12, E68.2
unnamed: E67.11, E68.4
unnamed: E68.8, E78.13
unnamed: E44.4, E56.1
unnamed: E23.6, E44.2
unnamed: E23.8, E43.2
unnamed: E23.12, E44.1
unnamed: E33.6, E43.1
unnamed: E33.8, E43.12
unnamed: E33.12, E43.3
VCC: C11.1, C12.1, C13.1, C14.1, C15.1, C16.1, C17.1, C18.1, C21.1, C22.1, C23.1, C24.1, C25.1, C26.1, C27.1, C28.1, C31.1, C32.1, C33.1, C34.1, C35.1, C36.1, C37.1, C38.1, C41.1, C42.1, C43.1, C44.1, C45.1, C46.1, C47.1, C48.1, C51.1, C52.1, C53.1, C54.1, C55.1, C56.1, C57.1, C58.1, C61.1, C62.1, C63.1, C64.1, C65.1, C66.1, C67.1, C68.1, C71.1, C72.1, C73.1, C74.1, C75.1, C76.1, C77.1, C78.1, C81.1, C82.1, C83.1, C84.1, C85.1, C86.1, C87.1, C88.1, C91.1, C92.1, C93.1, C94.1, C95.1, C96.1, C101.1, E11.20 (VCC), E12.1 (~Mr), E12.16 (VCC), E13.1 (~Mr), E13.16 (VCC), E14.16 (VCC), E15.16 (VCC), E16.16 (VCC), E17.16 (VCC), E18.16 (VCC), E21.20 (VCC), E22.1 (~MR), E22.16 (VCC), E23.14 (VCC), E24.16 (VCC), E25.16 (VCC), E26.16 (VCC), E27.16 (VCC), E28.16 (VCC), E31.20 (VCC), E32.4 (D0), E32.16 (VCC), E33.14 (VCC), E34.16 (VCC), E35.16 (VCC), E36.16 (VCC), E37.16 (VCC), E38.16 (VCC), E41.20 (VCC), E42.1 (~MR), E42.16 (VCC), E43.4, E43.5, E43.11, E43.14 (VCC), E44.14 (VCC), E45.1 (~Mr), E45.16 (VCC), E46.6 (E2), E46.16 (VCC), E47.14 (VCC), E48.14 (VCC), E51.20 (VCC), E52.1 (~Mr), E52.16 (VCC), E53.1 (~MR), E53.16 (VCC), E54.14 (VCC), E55.14 (VCC), E56.14 (VCC), E57.14 (VCC), E58.14 (VCC), E61.20 (VCC), E62.14 (VCC), E63.14 (VCC), E64.14 (VCC), E65.14 (VCC), E66.14 (VCC), E67.3, E67.4, E67.14 (VCC), E68.14 (VCC), E71.20 (VCC), E72.1 (~R), E72.4 (~S), E72.14 (VCC), E73.14 (VCC), E74.14 (VCC), E75.14 (VCC), E76.14 (VCC), E77.14 (VCC), E78.14 (VCC), E81.20 (VCC), E82.4 (~S), E82.14 (VCC), E83.14 (VCC), E84.14 (VCC), E85.14 (VCC), E86.14 (VCC), E87.14 (VCC), E88.14 (VCC), E91.20 (VCC), E92.14 (VCC), E93.14 (VCC), E94.16 (VCC), E95.14 (VCC), E96.11, E96.14 (VCC), E101.20 (VCC), J1.1, J2.1, J3.1, J4.1

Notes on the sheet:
RSEL 0 nop 1 BSW 2 RAL 3 RTL 4 RAR 5 RTR 6,7 zero
inc pc for isz instrs
// _MQUO_6
load pc for jms
load MBUF at end of TS1 with data read from memory
brkcyc sets at TS1 of break cycle clears at TS4 of all cycles
// _MQUO_1
// _MQUO_0
enable pc load at next pcclk
// _MQUO_3
Clear ACUM for Group1 CLA at TP2
clock in new MADR at TP4 except EXAM and DEPOS cycles
// _MQUO_11
// _SCTR_4
load pc for indir jmp
load pc for dir jmp
load pc when halted for ldad/exam/depos
load pc for intak
// _MQUO_7
// _MQUO_4
save overflow bit at TP2 * EXEC: used for ISZ skip must be valid until same TP3 * WRDCT: used for BWCOV must be valid until BREAK TP3
load MADR after a 2 cycle delay after LDAD,EXAM,DEPOS LDAD: loads from SR repeat EXAM/DEPOS: load MADR+1
inc pc after fetch
// _MQUO_5
// _MQUO_9
// _MQUO_2
inc pc for skip instrs
clock pc: ldad pressed tp2 during fetch tp3 must have pcinc or pcld to do anything else it is a nop
Clock ROTQ into ACUM at TP3 * FETCH of IOT instruction * EXEC of AND/TAD/DCA * FETCH of Group1,Group2 * ext arith execute
inc pc for i/o instrs
// _DMAFLD_1
// _MQUO_8
// _MQUO_10
inc pc for eae instrs
enable pc inc at next pcclk
load MBUF at end of TS2 with updated value to write to memory in TS3
current cycle is performing extended arithmetic accumulator and link get clocked at TP3 in these cycles FETCH: must have opcode 111 1xx xxx 001 EXEC: must have opcode 111 xxx xxx xxx it is the only OPR opcode that uses EXEC state
I2: RTR I3: RAR I4: RTL I5: RAL I6: BSW I7: nop

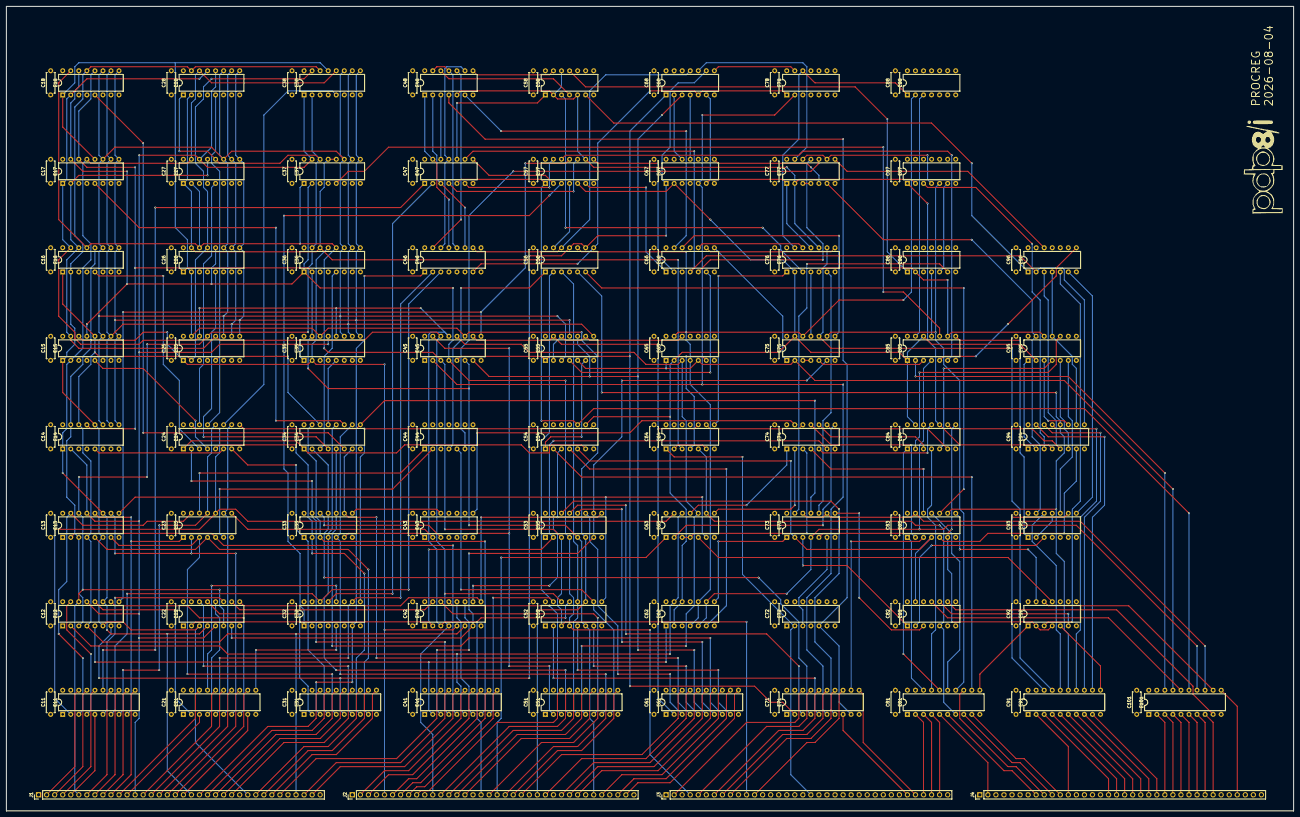
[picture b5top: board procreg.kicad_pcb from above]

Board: 4 copper layers, 406.4 x 254.0 mm, 146 parts (0 on the bottom side), 310 nets.
